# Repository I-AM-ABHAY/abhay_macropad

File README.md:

<div align="center">

<br><br><br>

<br><br><br><br><br><br>

<div align="left">

### About the Project

This project is a custom 9-key macropad that I designed and built from scratch. It uses a Seeed Studio XIAO RP2040 and KMK firmware to run programmable macros, shortcuts, and media controls. It also has a 128×32 OLED display that shows animations and status information, RGB LEDs that provide visual feedback for each key press, and a rotary encoder for volume control.

<br><br>

### Why I Built It

I wanted a macropad that matched the shortcuts I use every day instead of relying on a standard keyboard. I found myself constantly opening the same apps, taking screenshots, controlling media, and using the same keyboard shortcuts over and over. Building a macropad let me do all of that with a single key press.

I also wanted to learn more about hardware by building a complete project from scratch. So, I designed the PCB, modeled the case, wrote the firmware, assembled the hardware, and documented the entire process. By the end of the project, I had a macropad that I actually use while learning more about PCB design, CAD, embedded programming, and hardware development.

<br><br><br><br><br><br>

<div align="center">

### Sponsored By

<br><br>

</div>

<br><br><br><br><br>

<div align="center">

### Bill of Materials

<br>

<div align="center">

| Qty | Component                                                                            | Cost   |
| :-: | ------------------------------------------------------------------------------------ | ------ |
|  4x | [M2.5 Self-Tapping Screws](https://www.aliexpress.us/item/3256805544601650.html)     | $1.97  |
|  4x | [M3 Heat-Set Inserts](https://www.aliexpress.us/item/3256808480358197.html)          | $1.99  |
|  4x | [M3 Machine Screws](https://www.aliexpress.us/item/2255800784679048.html)            | $1.87  |
|  1x | [Seeed Studio XIAO RP2040](https://www.aliexpress.us/item/3256808014602728.html)     | $11.73 |
|  9x | [SK6812 MINI-E RGB LEDS](https://www.aliexpress.us/item/3256805007401420.html)       | $2.50  |
|  1x | [SSD1306 128×32 OLED Display](https://www.aliexpress.com/item/2251832623890853.html) | $1.52  |
|  9x | [Tactile Switches](https://www.aliexpress.us/item/3256808352947766.html)             | $3.50  |
|  9x | [Frosted Clear Keycaps](https://www.aliexpress.com/item/3256810359094598.html)       | $2.67  |
|  9x | [SOD-123 Diodes](https://www.aliexpress.us/item/3256805388348871.html)               | $1.53  |
| 11x | [1206 Capacitors](https://www.aliexpress.us/item/3256807177349573.html)              | $1.26  |
|  1x | [0805 Resistor](https://www.aliexpress.us/item/3256809618872827.html)                | $1.42  |
|  1x | [Bus Buffer Gate](https://www.aliexpress.us/item/3256807066238250.html)              | $1.51  |
|  1x | [Custom PCB](https://jlcpcb.com/)                                                    | $3.30  |
|  1x | 3D Printed Case (Printing Legion)                                                    | $0.00  |

<br>

**Parts Subtotal:** $34.77

**Fees  |  Tax** $0.65

**Grand Total:** $35.42

<br><br><br><br><br>

### PCB Schematic

<br>

<br><br>

### PCB Layout

<br>

<div align="center">

**Top Layer**

<br>

<br><br>

**Bottom Layer**

<br>

<br><br>

**3D View**

<br>

<br><br>

</div>

<br><br>

### Case Design

<br>

<div align="center">

**Top Case**

<br>

<br><br>

**Bottom Case**

<br>

</div>

<br><br>

### Final Assembly

<br>

<div align="center">

</div>

<br><br>

<div align="center">

*Designed and Built by Abhay P.*

</div>

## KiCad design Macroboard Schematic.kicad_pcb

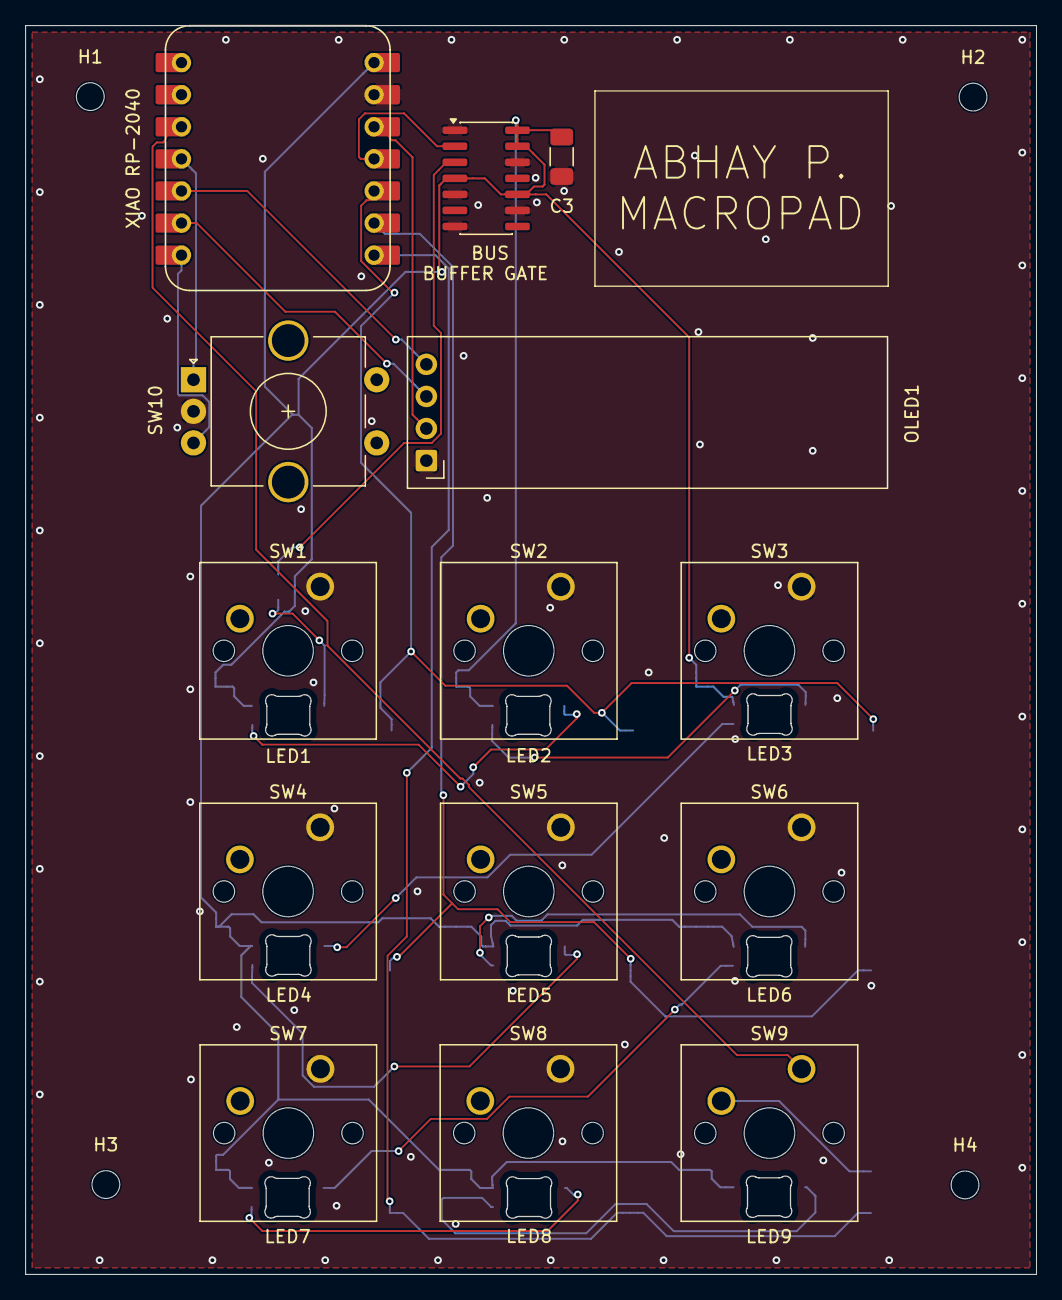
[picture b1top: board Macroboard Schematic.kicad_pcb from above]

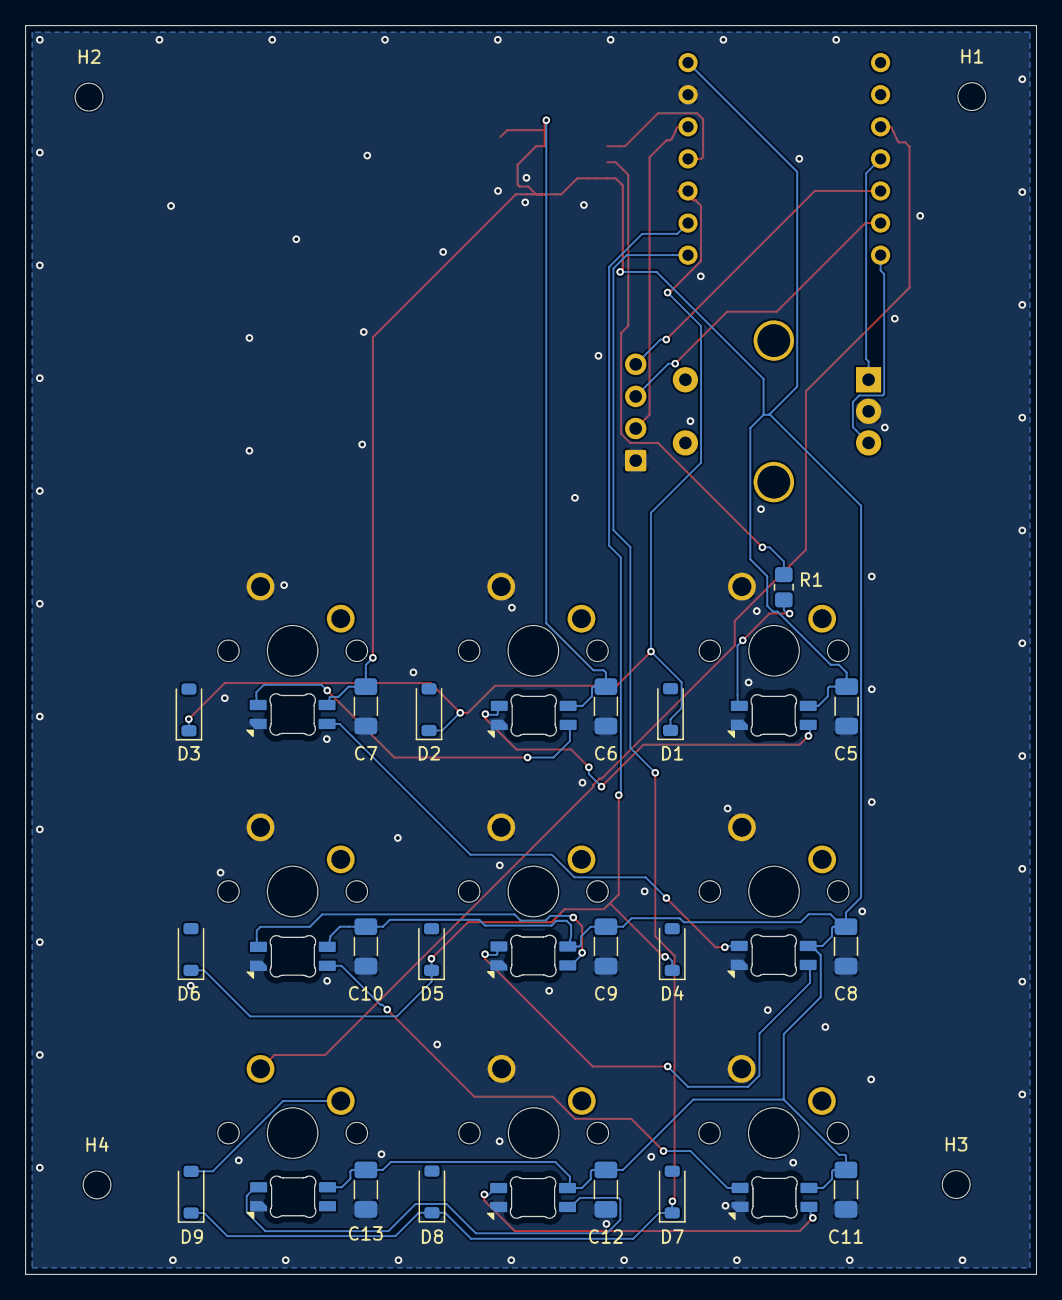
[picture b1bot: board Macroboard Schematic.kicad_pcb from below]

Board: 2 copper layers, 80.0 x 98.8 mm, 46 parts (28 on the bottom side), 23 nets.

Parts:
C3, C5, C6, C7, C8, C9, C10, C11, C12, C13: 100nF; C_1206_3216Metric_Pad1.33x1.80mm_HandSolder
D1, D2, D3, D4, D5, D6, D7, D8, D9: 1N4148W; D_SOD-123
H1, H2, H3, H4: MountingHole; MountingHole_2.2mm_M2
LED1, LED2, LED3, LED4, LED5, LED6, LED7, LED8, LED9: MX_SK6812MINI-E; LED_MX_6028R
OLED1: ER_OLEDM0.91_1x-I2C
R1: 330R; R_0805_2012Metric_Pad1.20x1.40mm_HandSolder
SW1, SW2, SW3, SW4, SW5, SW6, SW7, SW8, SW9: SW_Push; SW_Cherry_MX_1.00u_PCB
SW10: RotaryEncoder; RotaryEncoder_Alps_EC11E-Switch_Vertical_H20mm_CircularMoun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
U1: 74AHCT125; SOIC-14_3.9x8.7mm_P1.27mm
U3: XIAO-RP2040-DIP

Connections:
+3.3V: OLED1.2 (VCC), U3.12 (3V3)
+5V: C3.2, C5.2, C6.2, C7.2, C8.2, C9.1, C10.2, C11.2, C12.1, C13.2, LED1.1 (VDD), LED2.1 (VDD), LED3.1 (VDD), LED4.1 (VDD), LED5.1 (VDD), LED6.1 (VDD), LED7.1 (VDD), LED8.1 (VDD), LED9.1 (VDD), U1.4, U1.10, U1.13, U1.14 (VCC), U3.14 (VBUS)
COLUMN 3: SW9.1, U3.3 (P28_A2_D2)
ENCODER A: SW10.A, U3.4 (P29_A3_D3)
ENCODER B: SW10.B, U3.7 (P0_D6_TX)
GND: C3.1, C5.1, C6.1, C7.1, C8.1, C9.2, C10.1, C11.1, C12.2, C13.1, LED1.3 (VSS), LED2.3 (VSS), LED3.3 (VSS), LED4.3 (VSS), LED5.3 (VSS), LED6.3 (VSS), LED7.3 (VSS), LED8.3 (VSS), LED9.3 (VSS), OLED1.1 (GND), SW1.1, SW2.1, SW3.1, SW4.1, SW5.1, SW6.1, SW7.1, SW8.1, SW10.C, U1.1, U1.5, U1.7 (GND), U1.9, U1.12, U3.13 (GND)
LED: U1.2, U3.11 (P3_D10_MOSI)
unnamed: D9.2 (A), SW9.2
unnamed: LED1.4 (DIN), R1.2
unnamed: LED1.2 (DOUT), LED2.4 (DIN)
unnamed: LED2.2 (DOUT), LED3.4 (DIN)
unnamed: LED3.2 (DOUT), LED4.4 (DIN)
unnamed: LED4.2 (DOUT), LED5.4 (DIN)
unnamed: LED5.2 (DOUT), LED6.4 (DIN)
unnamed: LED6.2 (DOUT), LED7.4 (DIN)
unnamed: LED7.2 (DOUT), LED8.4 (DIN)
unnamed: LED8.2 (DOUT), LED9.4 (DIN)
unnamed: R1.1, U1.3
ROW 1: D1.1 (K), D2.1 (K), D3.1 (K), U3.10 (P4_D9_MISO)
ROW 2: D4.1 (K), D5.1 (K), D6.1 (K), U3.9 (P2_D8_SCK)
ROW 3: D7.1 (K), D8.1 (K), D9.1 (K), U3.8 (P1_D7_RX)
SCL: OLED1.3 (SCL), U3.6 (P7_SCL_D5)
SDA: OLED1.4 (SDA), U3.5 (P6_SDA_D4)

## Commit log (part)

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2026-05-22 Update README with bill of materials and images
    Added detailed bill of materials and updated images for various components.
2026-05-22 Rename Macroboard Schematic.kicad_sch to PCB/Macroboard Schematic.kicad_sch
2026-05-22 Enhance README with HTML line breaks
    Updated the description to include HTML line breaks.
2026-05-30 Add journal entries for macroboard project
    Documented the process of creating a macroboard, including schematic design, 3D modeling, assembly, firmware coding, sourcing parts, and final submission.
2026-05-30 Update cost breakdown with shipping and tax
    Added shipping and tax details to the cost breakdown.
2026-05-31 Refactor firmware for macro board with encoder support
2026-05-31 Refactor OLED handling and improve LED system
2026-06-01 Rename FIRMWARE.md to FIRMWARE_DOCUMENTATION.md
2026-06-01 Rename macroboardfirmware.py to macropadfirmware.py
2026-06-01 Rename FIRMWARE_DOCUMENTATION.md to macropad_firmware_documentation.md
2026-06-01 Rename MACROPAD BOTTOM CASE.step to macropad_bottom_case.step
2026-06-01 Rename MACROPAD TOP CASE.step to macropad_top_case.step
2026-06-01 Rename macropad_gbr_drl_files.zip to GBR_DRILL_FILES/ macropad_gbr_drl_files.zip
2026-06-01 Rename MACROPAD GBR AND DRL FILES macropad_gbr_drl_files.zip to MACROPAD GBR AND DRL FILES/ macropad_gbr_drl_files.zip
2026-06-01 Rename Macroboard Schematic.kicad_pcb to Macroboard Schematic.kicad_pcb
2026-06-01 Rename Macroboard Schematic.kicad_sch to Macroboard Schematic.kicad_sch
2026-06-01 Rename macropad_bottom_case.step to macropad_bottom_case.step
2026-06-01 Rename macropad_top_case.step to macropad_top_case.step
2026-06-01 Rename macropad_firmware_documentation.md to macropad_firmware_documentation.md
2026-06-01 Rename macropad_gbr_drl_files.zip to macropad_gbr_drl_files.zip
2026-06-01 Rename macropad_gbr_drl_files.zip to macropad_gbr_drl_files.zip
2026-06-01 Rename macroboard_assembly.f3z to macroboard_assembly.f3z
2026-06-03 Rename Macroboard Schematic.kicad_pcb to 1_PCB FILES/Macroboard Schematic.kicad_pcb
2026-06-03 Rename Macroboard Schematic.kicad_pro to 1_PCB FILES/Macroboard Schematic.kicad_pro
2026-06-03 Rename Macroboard Schematic.kicad_sch to 1_PCB FILES/Macroboard Schematic.kicad_sch
2026-06-04 Rename Macroboard .kicad_sch to 1_PCB FILES/Macroboard .kicad_sch
2026-06-04 Rename Macroboard.kicad_pcb to 1_PCB FILES/Macroboard.kicad_pcb
2026-06-04 Rename Macroboard.kicad_pro to 1_PCB/FILESMacroboard.kicad_pro
2026-06-04 Rename FILESMacroboard.kicad_pro to Macroboard.kicad_pro
2026-06-04 Update print statement from 'Hello' to 'Goodbye'
2026-06-04 Add firmware documentation for macropad system
    Added comprehensive documentation for the macropad firmware, detailing hardware components, key mapping, system flow, and functionality.
2026-06-04 Rename firmware_documentation to firmware_documentation.md
2026-06-04 Rename macropadfirmware.py to macropad_firmware.py
2026-06-04 Rename MACROBOARD GBR AND DRL FILES.zip to GBR | DRL FILES.zip
2026-06-04 Rename Macroboard .kicad_sch to Macroboard .kicad_sch
2026-06-04 Rename Macroboard.kicad_pcb to Macroboard.kicad_pcb
2026-06-04 Rename Macroboard.kicad_pro to Macroboard.kicad_pro
2026-06-04 Rename GBR | DRL FILES.zip to GBR | DRL FILES/macropad GBR | DRL files.zip
2026-06-04 Rename firmware_documentation.md to FIRMWARE FILES/firmware_documentation.md
2026-06-04 Rename macropad_firmware.py to FIRMWARE FILES/macropad_firmware.py
2026-06-04 Rename MACROPAD BOTTOM CASE.step to CAD FILES/MACROPAD BOTTOM CASE.step
2026-06-04 Rename MACROPAD TOP CASE.step to CAD FILES/MACROPAD TOP CASE.step
2026-06-04 Rename macropad assembly.f3z to CAD FILES/macropad assembly.f3z
2026-06-04 Rename CAD FILES/macropad assembly.f3z to CAD FILES/ASSEMBLY/macropad assembly.f3z
2026-06-07 Rename bom.csv to BOM.csv
2026-06-09 Rename Macroboard Schematic.kicad_pcb to PCB FILES/Macroboard Schematic.kicad_pcb
2026-06-09 Rename Macroboard Schematic.kicad_pro to PCB FILES/Macroboard Schematic.kicad_pro
2026-06-09 Rename Macroboard Schematic.kicad_sch to PCB FILES/Macroboard Schematic.kicad_sch
2026-06-10 Fix typo in README.md from 'MC' to 'MCU'
2026-06-18 Update README formatting and component descriptions
2026-06-23 Fix formatting in README.md table
2026-06-23 Update hardware specifications in README
2026-06-30 Refactor journal entries for clarity and conciseness
    Revised the journal entries for clarity and conciseness, maintaining the original content while improving readability. Updated images and links for better accessibility.
2026-06-30 Add 'Why I Built This' section to README
    Added a section explaining the motivation behind building the macropad, including personal use cases and learning objectives.
